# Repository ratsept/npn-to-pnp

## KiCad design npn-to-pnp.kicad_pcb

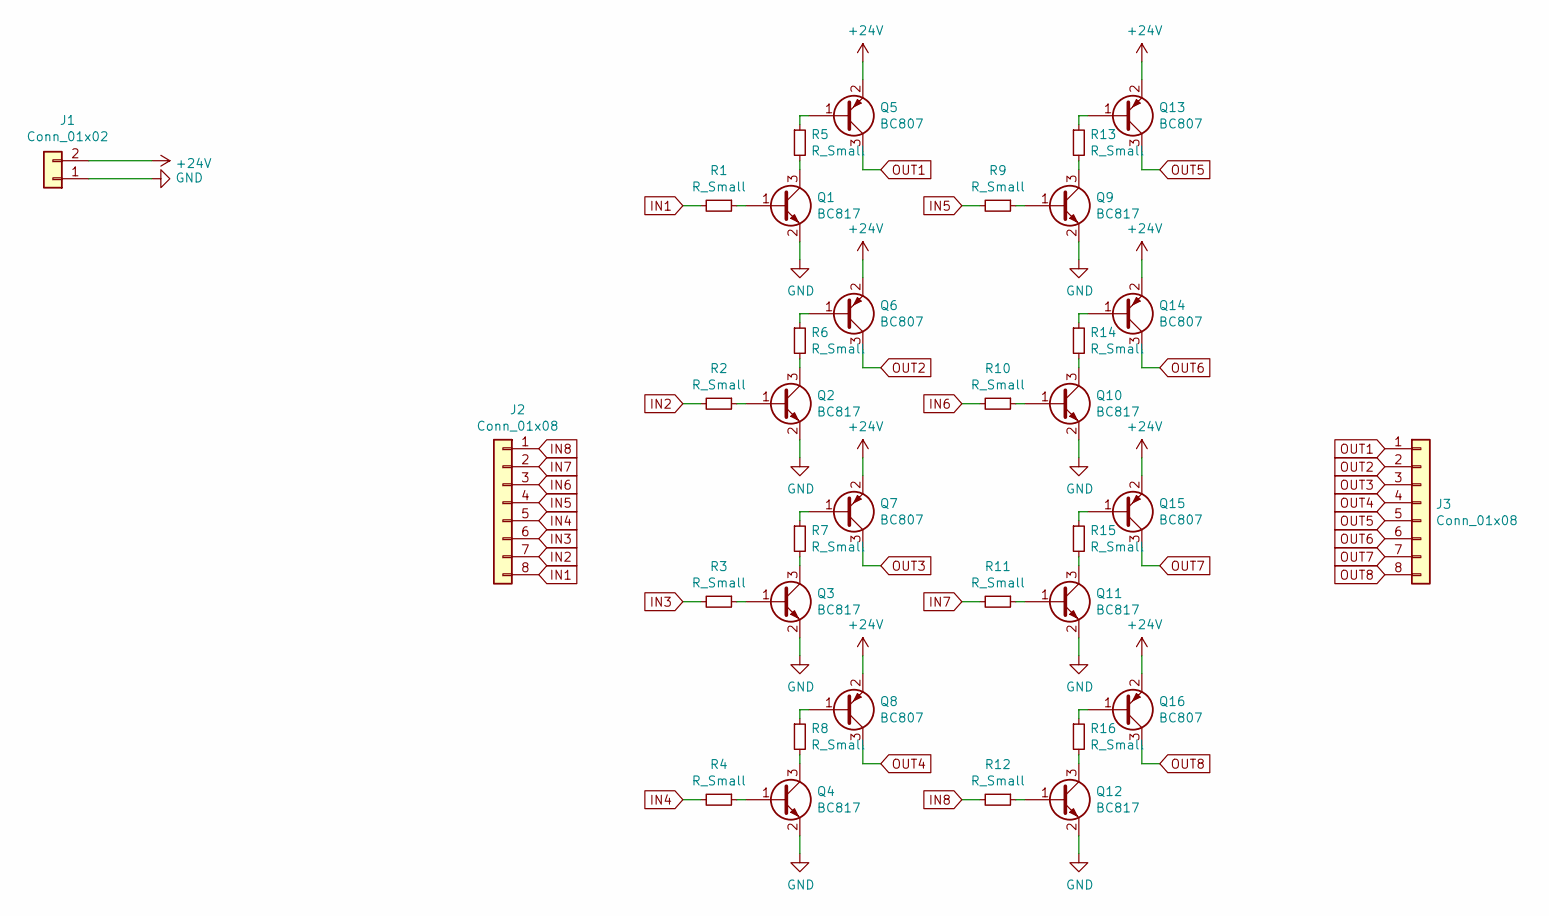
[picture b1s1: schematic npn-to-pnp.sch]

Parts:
J1: Conn_01x02; TerminalBlock_RND_205-00232_Pitch5.08mm
J2, J3: Conn_01x08; TerminalBlock_RND_205-00238_Pitch5.08mm
Q1, Q2, Q3, Q4, Q9, Q10, Q11, Q12: BC817; SOT-23
Q5, Q6, Q7, Q8, Q13, Q14, Q15, Q16: BC807; SOT-23
R1, R2, R3, R4, R5, R6, R7, R8, R9, R10, R11, R12, R13, R14, R15, R16: R_Small; R_0805_HandSoldering

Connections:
+24V: J1.2, Q5.2 (E), Q6.2 (E), Q7.2 (E), Q8.2 (E), Q13.2 (E), Q14.2 (E), Q15.2 (E), Q16.2 (E)
GND: J1.1, Q1.2 (E), Q2.2 (E), Q3.2 (E), Q4.2 (E), Q9.2 (E), Q10.2 (E), Q11.2 (E), Q12.2 (E)
IN1: J2.8, R1.2
IN2: J2.7, R2.2
IN3: J2.6, R3.2
IN4: J2.5, R4.2
IN5: J2.4, R9.2
IN6: J2.3, R10.2
IN7: J2.2, R11.2
IN8: J2.1, R12.2
unnamed: Q1.1 (B), R1.1
unnamed: Q1.3 (C), R5.2
unnamed: Q2.1 (B), R2.1
unnamed: Q2.3 (C), R6.2
unnamed: Q3.1 (B), R3.1
unnamed: Q3.3 (C), R7.2
unnamed: Q4.1 (B), R4.1
unnamed: Q4.3 (C), R8.2
unnamed: Q5.1 (B), R5.1
unnamed: Q6.1 (B), R6.1
unnamed: Q7.1 (B), R7.1
unnamed: Q8.1 (B), R8.1
unnamed: Q9.1 (B), R9.1
unnamed: Q9.3 (C), R13.2
unnamed: Q10.1 (B), R10.1
unnamed: Q10.3 (C), R14.2
unnamed: Q11.1 (B), R11.1
unnamed: Q11.3 (C), R15.2
unnamed: Q12.1 (B), R12.1
unnamed: Q12.3 (C), R16.2
unnamed: Q13.1 (B), R13.1
unnamed: Q14.1 (B), R14.1
unnamed: Q15.1 (B), R15.1
unnamed: Q16.1 (B), R16.1
OUT1: J3.1, Q5.3 (C)
OUT2: J3.2, Q6.3 (C)
OUT3: J3.3, Q7.3 (C)
OUT4: J3.4, Q8.3 (C)
OUT5: J3.5, Q13.3 (C)
OUT6: J3.6, Q14.3 (C)
OUT7: J3.7, Q15.3 (C)
OUT8: J3.8, Q16.3 (C)

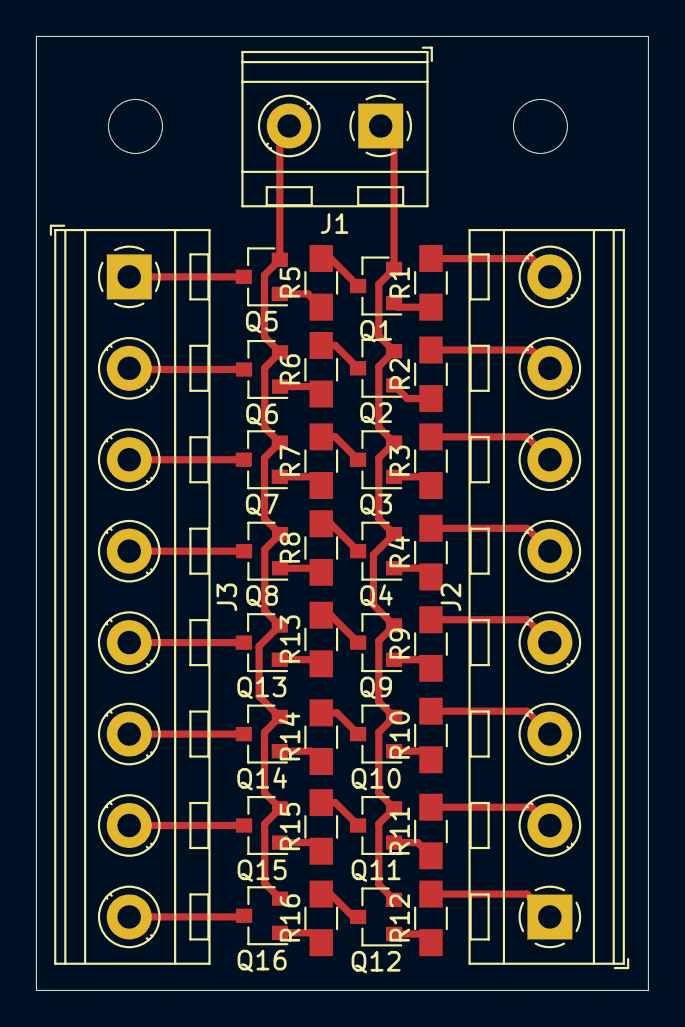
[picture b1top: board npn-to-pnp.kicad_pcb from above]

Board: 2 copper layers, 34.0 x 53.0 mm, 35 parts (0 on the bottom side), 42 nets.

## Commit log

2021-06-08 2021-06-08
